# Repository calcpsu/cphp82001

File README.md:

# CalcPack HP 82001

A Li-Po battery replacement design for HP35/HP45/HP55/HP65/HP67 calculators. The original batteries had ~ 500mAh capacity, while modern Ni-MH replacements are typically ~1500mAh.

Li-Po has the advantage of far reduced self-discharge in comparison to Ni-MH, which is an advantage for an intermittently-used device. Even with similar mAh capacity, we can expect longer battery life.

Ni-MH / Ni-CD batteries are notorious for leaking. While Lithium Ion batteries are notorious for self-immolation, a well protected Li-Po battery (particularly in a low current application like this) should be able to be made very safe.

## Features / design goals:
- Fit into existing compartment with no modifications
- Similar or ideally exceed capacity of standard Ni-Cd or Ni-MH 3xAA types (1200~2200mAh)
- Dual charge - USB (externally) or in-place using original HP charger
- Battery charge control and protection
- Maximise battery life:
    - Minimise Iq to maximise time between charges (shelf time)
    - Minimise voltage drop / series resistance of circuits to maximise run time
    - Optimise Vout to minimise calculator power consumption

## References 
This has been inspired by the below reference projects:
 - https://www.edn.com/classic-hp-35-calculator-comes-back-to-life/
   - GOOD: Regulated (see reasoning in the article, and discussion below)
   - BAD: Has no charging circuit / must remove to charge
   - BAD: Cannot connect HP charger (would cause dangerous overcharge condition; best case trip battery OC protection)
 - https://hackaday.io/project/175815-classic-hp-calculator-lipo-battery-pack
   - GOOD: Has on-board charge controller
   - BAD: Has no regulation
   - GOOD: Can connect HP charger, but
   - BAD: Unable to charge from HP charger / must remove to charge

## Key Components
If you're looking for a full BOM, please check the main files.
A digikey list is provided here for convenience (no guarantees!): [calcpsu cphp82001](https://www.digikey.com.au/en/mylists/list/Z6K09H5IB0)
 - Battery:
     - 10x34x50mm lipo pouch cell. These also include a DW01A/FS8205 protection circuit.
 - Charge controller: [BQ21040](https://www.ti.com/lit/ds/symlink/bq21040.pdf)
     - Wide voltage input range (over voltage protected)
     - Clever voltage foldback mode (which will help with constant current supply charging)
     - Variable current setting
     - Safety timer (10h) and 10% termination current
 - OPTION 1: Regulator: [TLV75801](https://www.ti.com/lit/ds/symlink/tlv758p.pdf)
     - Ultra low dropout (~30mV)
     - 500mA current limited (enough for HP67 card read/write at ~400mA for a few seconds)
     - Very low Iq for a regulator (25uA at idle, assuming Vb > Vo; only 400uA or so at full current)
     - Note: option eliminated as of REV5; if you're really keen for a regulated version please to check out rev4.
 - OPTION 2: Current Limiter: [MCP380SNT](https://www.onsemi.com/pdf/datasheet/ncp380-d.pdf)
     - Designed as a USB input current limiter, also works for LiPo cell voltage range
     - 800mA limiting, short circuit protection
     - Provides the similar current limiting capability as the TLV75801 with minimal additional quiescent current; allows retaining this function/protection in case of an unregulated option.
 - Output protection diode: [MAX40203](https://www.analog.com/media/en/technical-documentation/data-sheets/MAX40203.pdf)
     - Low voltage drop (~40mV) ideal diode
     - Low leakage and low Iq (<0.5uA)
 - Undervoltage protection: [APX809S-31SA](https://www.diodes.com/assets/Datasheets/APX809S-810S.pdf)
     - Pre-set with 3.1V threshold
     - Output used to shutdown regulator, shutting off load and vastly reducing Iq
     - Actual protective disconnection of battery done at ~2.5V by battery pack protection circuit (typically DW01A/FS8205)
 - Input overvoltage protection: [NCP360SNT](https://www.onsemi.com/pdf/datasheet/ncp360-d.pdf)
     - Cuts off USB input for overvoltage condition (note that 2x rated voltage is required by compliance test standard EN38.3 T.7, required for transport of lipo batteries in USA/EU).
     - Input via pads does not require OVP - it can tolerate the required 22v/100mA required condition.

## Function Description

### Discharging, calculator on:
 - B+ supplies cell voltage via current limiting IC
 - Output delivered to calculator via ideal diode U3
 - Vout at 3.8V is below threshold for U4 (4.4V), Q2 is off and VCC is 0V (charging IC shutdown completely)
### Charging, USB:
 - VBUS supplies VCC via U6 and D1
 - Presence of VBUS pulls prog down via Q1, charge controller now charges battery at higher current (0.2C target)
 - Physically not possible to do inside the calculator, can assume calculator is not connected during charging.
   - Although, body diode of Q2 and U3 would enable effective load sharing in this case, with output at about 4V (still well within acceptable limits for the calculator). This could be used for a future alternative in-system charging connection (e.g. a modified charging circuit, wireless charging, etc.)
### Charging, HP charger:
 - HP charger supplies 50mA constant current, up to 16V (!!). With the original NiCads, these acted as a voltage clamp (float charge about 1.43V/cell = 4.3V) - we need to replace this function.
    - With no charging current, voltage Vout rises until U3 switches off.
    - Will continue to rise until clamped by D2 (this should be low enough to protect HP65/67 sense chip from harm with extended application, but too low will result in excessive Iq as the voltage nears the zener's knee). Reviewing available documents, 4.3V is definitely OK, 6.25V might be survivable (as this is Vss normally). I have tested with 5.6V zener, and this has shown no negative impact to any calculators (particualrly the HP-67, where the sense chip sees this voltage, albeit when off).
    - Exceeding 4.4V for 240ms, U4 activates and connects Vout to Vcc via Q2 and D4.
    - D4 ensures that U1 throttles current (Vcc below 4.3V) before U4 cuts off supply (VOUTF 4.4V), maximising utilisation of limited constant current supply. See further explanation in [issue #5](https://github.com/calcpsu/cphp82001/issues/5).
    - U1 begins charge cycle, delivering up to 50mA to battery.
    - On charge termination, VCC current is minimal (10's of uA), all 50mA will be running through D2 (~0.25W power; using biggest one I can fit to keep temperature down). Voltage will be at the zener voltage (5.6V).
 - HP35/45/55 calculators do not draw current when on - supplied separately by HP AC adapter, the calculator supply is physically disconnected from the charging circuit.
 - HP65/67 with card reader: card reader may draw from battery supply. The sense chip is connected to the battery continuously, and will see up to the 5.6V float voltage. In case the calculator is operated and this draws current, the CC supply voltage will drop until U4 shuts off current to the charge circuit, resetting the charge cycle. When VOUT drops below B+, U3 activates, and card reader is powered from the current limiter (B+). As the AC adapter is not sufficient to run the card reader, this is the least worst outcome available.
### Battery Exhausted:
 - HP35 shows low battery (decimal points) indication at V+ of 3.50V.
   - This represents about 6-7% charge state of LiPo
   - User may switch off and recharge now...
 - HP67 will show indicator at about 3.60V; similar to above but a little more margin.
 - HP35 will cease to function at ~3.25V, still draws ~75mA
   - User probably should switch off and recharge now...
 - U4 protects battery at VB+ = 3.1V, by disabling the regulator or current limiting IC. Iq should be ~10uA.
 - If left for a _really_ long time, VB+ may reduce to 2.5V, which should trigger battery pack protection circuit and fully disconnect the battery. Plugging in (turning on charge controller, which will do a battery detection routine and reset the protection circuit) will reset.

## Assembly Notes ##

Refer to the schematic for details. The following notes are worth considering if building your own:
* The design up to v4 allows either regulated or unregulated option. From v5, only unregulated is supported (and recommended, see below).
  - For regulated (best for HP35), U2 regulator provides regulation and current limiting - U7 is not required and can be omitted and bypassed.
  - For unregulated (best for all later types), U2 is omitted and bypassed, and U7 is added to provide current limiting
* Digikey list is [here](https://www.digikey.com.au/en/mylists/list/Z6K09H5IB0)
* A 3-pin JST-SH (1.0mm pitch) connector is used for the battery. 1=pos, 2=temp, 3=neg
  - R13 is in parallel with TS pin NTC thermistor. If the battery does not a provide NTC thermistor (white wire, 3 pin connector), leave pin2 open and install R13=10k.
  - Note datasheet indicates 237k resistor prevents timer disable mode, but this also prevents charging without thermistor
    
| R13 | Battery With Temperature Sensor | Battery Without Temperature Sensor |
| --- | --- | --- |
| Omit | 🟢 10% Current Charge Termination <br> 🟢 10h Charge Timeout | 🔴 10% Current Charge Termination <br> 🔴 10h Charge Timeout |
| 10k  | ⚠️ Will not charge T>25C <br> ⚠️ Will charge T<0C  | 🟢 10% Current Charge Termination <br> 🟢  charge timeout |

* Two case sizes are provided:
    * 8mm suits 8mm thick batteries (1500mAh)
    * 10mm suits 10mm thick batteries (2000mAh), but it has been noted this can be a tight fit in some calculators
* Variants of each case, with and without an LED hole, are provided. If you 3D print with a transluscent material, the hole is not needed!

## Notes on optimisation:

Addition of a series regulator is not an immediately obvious means to maximise efficiency. I've measured the HP-35 increases current consumption as voltage rises (this is most likely a result of the way the LEDs are driven with fixed-duty inductive energy, this appears as brighter leds). Even accounting for the linear loss and Iq of the regulator circuit, total power consumption decreases as the regulator voltage decreases (down to about 3.6V, the minimum to operate the calculator reliably). The newer models (HP-45, HP-67) do the opposite - the current drops as the voltage increases, which indicates a more typical profile for a switchmode converter. The HP-67 has a card reader with a motor; this draws around 400mA when reading/writing a card, direct from battery. To allow for a little drop in the system, the regulator voltage needs to be a touch higher (looks like about 3.8V works consistently).

### Why not a switching regulator?

In theory, replacing the series linear regulator with a switching regulator may allow use of the battery capacity right down to 3.1V, and more efficiently use the currently wasted energy of the full battery (VB+ > 3.78V) currently being dissipated by the linear reg.

I've investigated using a MIC2250 step-up regulator, which has a surprisingly low Iq (55uA, not switching), and could provide a consistent output voltage right down to the end of the battery capacity (Vb=3.0V). At the currents needed, this can be around 87% efficient. This would provide a consistent voltage right up until shutdown. While this might be good particularly for the HP-67 card reader, it has the disadvantage of skipping the calculator's built-in low battery indication - the power supply unit would completely shutdown without any warning with a low battery.

### Model of 3 options

I've done a simulation of the 3 options:

  1. No regulator (default - calculator supplied with battery voltage via MAX40203 diode)
  2. Linear regulator (TLV75801, set to 3.80V)
  3. Switchmode step-up regulator (MIC2250, set to 3.80V also)

For each, the model calculates the change in output voltages given the battery state, calculator and power supply current draw, and iterates until the battery (2000mAh) is exhausted. The calculator load is measured from 3 sample calculators (HP-35, HP-45 and HP-67), reflecting the calculator being left on in the default display ("0." or "0.00" depending on the model), and accounts for the changing current with changing supply voltage. Results are shown below.

In summary, a regulated design gains a slight advantage in run time for the HP-35, while slightly reducing run time for HP-45 and HP-67. The switchmode design is actually best for the current-hungry HP-67, but not by a significant amount, and at the cost of higher quiescent current (shortening standby time significantly).

In conclusion, the regulated design provides a slight advantage for the HP-35 based on this model, however the unregulated design (with addition of necessary output short-circuit protection / current limiter) can be expected to be ideal for other models. Prototype testing with rev 3.5 showed the unregulated design works well in all the calculators, and the regulated design had noticeably faster self-discharge in practice, particularly as the quiescent current is larger than anticipated in dropout mode. As such, further designs have eliminated the regulator in favour of improved board layout and ease of use.

#### Results summary (t in hours)

#### HP-35

#### HP-45

#### HP-67

## Community Builds ##
Built one? Send me some pics and I'll share here!
### [Milo van der Zee](https://github.com/MilovdZee) ###

## License

This work is licensed under a
[Creative Commons Attribution-NonCommercial-ShareAlike 4.0 International License][cc-by-nc-sa].

[![CC BY-NC-SA 4.0][cc-by-nc-sa-image]][cc-by-nc-sa]

[cc-by-nc-sa]: http://creativecommons.org/licenses/by-nc-sa/4.0/
[cc-by-nc-sa-image]: https://licensebuttons.net/l/by-nc-sa/4.0/88x31.png
[cc-by-nc-sa-shield]: https://img.shields.io/badge/License-CC%20BY--NC--SA%204.0-lightgrey.svg

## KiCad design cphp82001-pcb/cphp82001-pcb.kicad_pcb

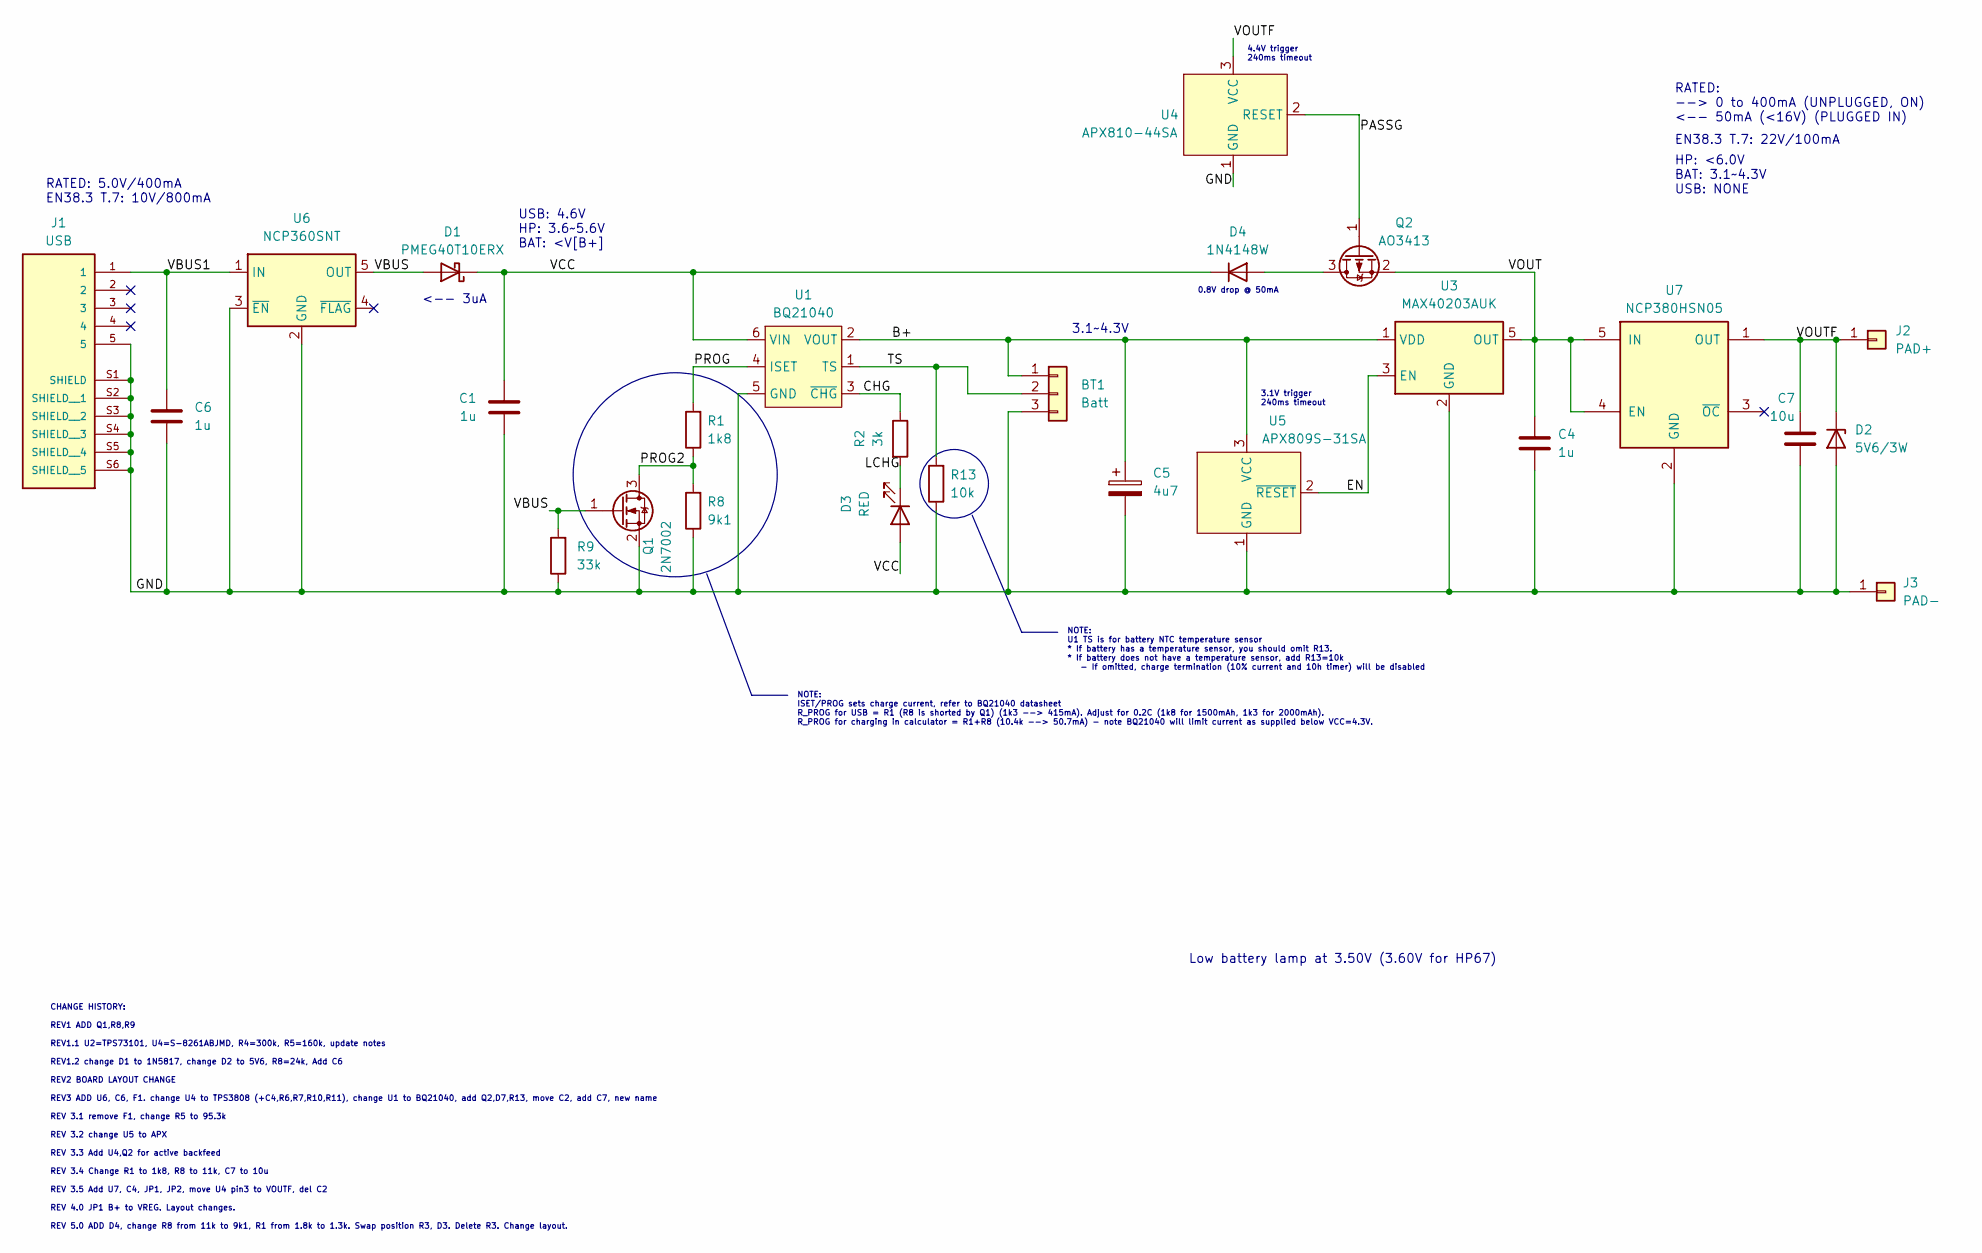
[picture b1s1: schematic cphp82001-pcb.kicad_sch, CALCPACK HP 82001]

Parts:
BT1: Batt; JST_SH_BM03B-SRSS-TB_1x03-1MP_P1.00mm_Vertical_13PADS
C1, C4, C6: 1u; C_0805_2012Metric
C5: 4u7; C_0805_2012Metric
C7: 10u; C_0805_2012Metric
D1: PMEG40T10ERX; D_SOD-123
D2: 5V6/3W; D_SMA
D3: RED; LED_0805_2012Metric
D4: 1N4148W; D_SOD-123
J1: USB; AMPHENOL_10118194-0001LF; PARTREV D
J2: PAD+; PAD_8x15
J3: PAD-; PAD_8x15
Q1: 2N7002; SOT-23
Q2: AO3413; SOT-23
R1: 1k8; R_0805_2012Metric
R2: 3k; R_0805_2012Metric
R8: 9k1; R_0805_2012Metric
R9: 33k; R_0805_2012Metric
R13: 10k; R_0805_2012Metric
U1: BQ21040; SOT-23-6_TI_DBV6
U3: MAX40203AUK; SOT-23-5_TI_DBV5
U4: APX810-44SA; SOT-23-3
U5: APX809S-31SA; SOT-23-3
U6: NCP360SNT; SOT-23-5_TI_DBV5
U7: NCP380HSN05; SOT-23-5_TI_DBV5

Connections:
/B+: BT1.1, C5.1, U1.2 (VOUT), U3.1 (VDD), U5.3 (VCC)
/CHG: R2.1, U1.3 (~CHG)
/EN: U3.3 (EN), U5.2 (~RESET)
/GND: BT1.3, C1.2, C4.2, C5.2, C6.2, C7.2, D2.2 (A), J1.5, J1.S1 (SHIELD), J1.S2 (SHIELD__1), J1.S3 (SHIELD__2), J1.S4 (SHIELD__3), J1.S5 (SHIELD__4), J1.S6 (SHIELD__5), J3.1, Q1.2 (S), R8.1, R9.1, R13.1, U1.5 (GND), U3.2 (GND), U4.1 (GND), U5.1 (GND), U6.2 (GND), U6.3 (~EN), U7.2 (GND)
/LCHG: D3.1 (K), R2.2
/PASSG: Q2.1 (G), U4.2 (RESET)
/PROG: R1.2, U1.4 (ISET)
/PROG2: Q1.3 (D), R1.1, R8.2
/TS: BT1.2, R13.2, U1.1 (TS)
/VBUS: D1.2 (A), Q1.1 (G), R9.2, U6.5 (OUT)
/VBUS1: C6.1, J1.1, U6.1 (IN)
/VCC: C1.1, D1.1 (K), D3.2 (A), D4.1 (K), U1.6 (VIN)
/VOUT: C4.1, Q2.2 (S), U3.5 (OUT), U7.4 (EN), U7.5 (IN)
/VOUTF: C7.1, D2.1 (K), J2.1, U4.3 (VCC), U7.1 (OUT)
unnamed: D4.2 (A), Q2.3 (D)

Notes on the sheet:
<-- 3uA
NOTE: ISET/PROG sets charge current, refer to BQ21040 datasheet R_PROG for USB = R1 (R8 is shorted by Q1) (1k3 --> 415mA). Adjust for 0.2C (1k8 for 1500mAh, 1k3 for 2000mAh). R_PROG for charging in calculator = R1+R8 (10.4k --> 50.7mA) - note BQ21040 will limit current as supplied below VCC=4.3V.
HP: <6.0V BAT: 3.1~4.3V USB: NONE
EN38.3 T.7: 22V/100mA
3.1V trigger 240ms timeout
RATED: --> 0 to 400mA (UNPLUGGED, ON) <-- 50mA (<16V) (PLUGGED IN)
USB: 4.6V HP: 3.6~5.6V BAT: <V[B+]
3.1~4.3V
NOTE: U1 TS is for battery NTC temperature sensor * If battery has a temperature sensor, you should omit R13. * If battery does not have a temperature sensor, add R13=10k - If omitted, charge termination (10% current and 10h timer) will be disabled
4.4V trigger 240ms timeout
RATED: 5.0V/400mA EN38.3 T.7: 10V/800mA
0.8V drop @ 50mA
CHANGE HISTORY: REV1 ADD Q1,R8,R9 REV1.1 U2=TPS73101, U4=S-8261ABJMD, R4=300k, R5=160k, update notes REV1.2 change D1 to 1N5817, change D2 to 5V6, R8=24k, Add C6 REV2 BOARD LAYOUT CHANGE REV3 ADD U6, C6, F1. change U4 to TPS3808 (+C4,R6,R7,R10,R11), change U1 to BQ21040, add Q2,D7,R13, move C2, add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
Low battery lamp at 3.50V (3.60V for HP67)

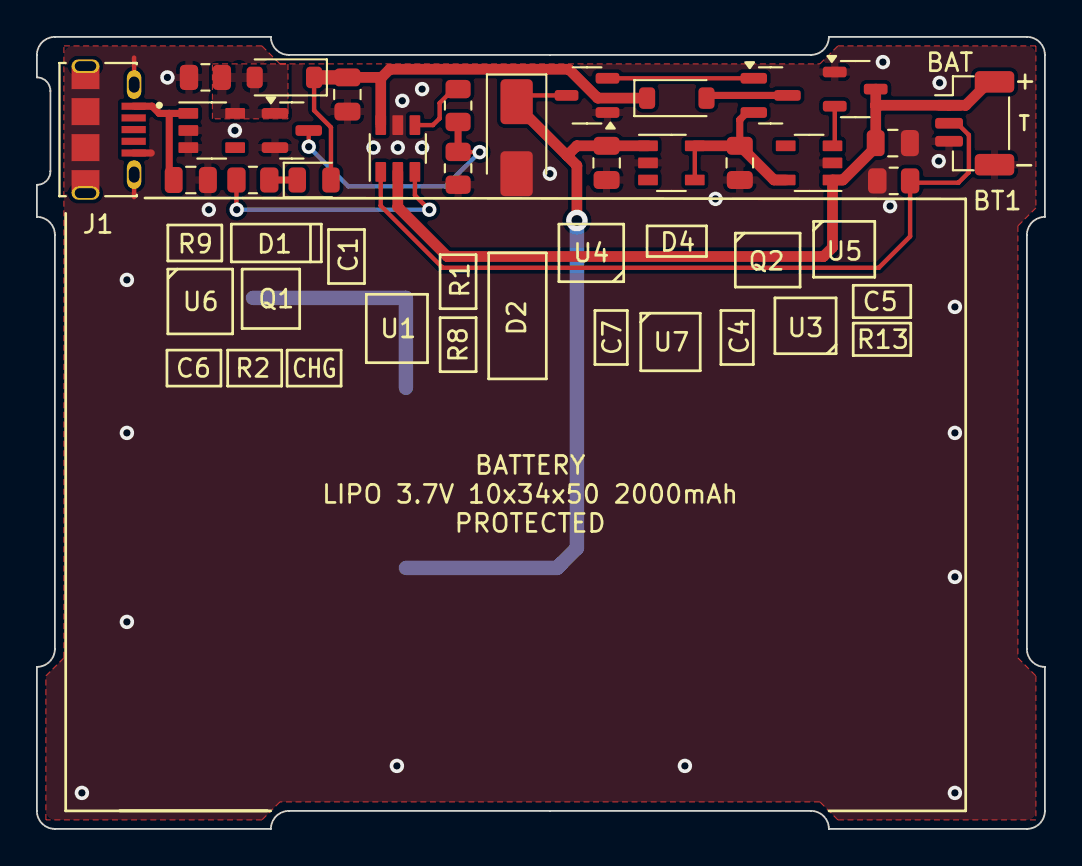
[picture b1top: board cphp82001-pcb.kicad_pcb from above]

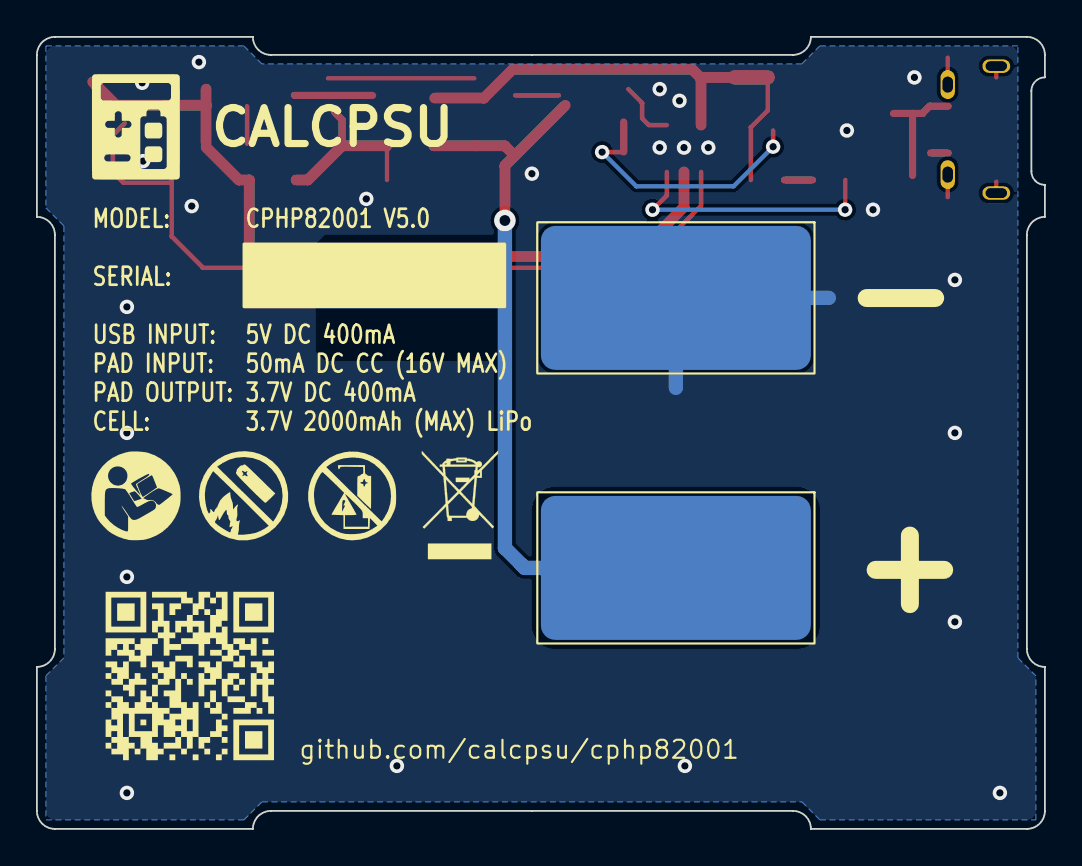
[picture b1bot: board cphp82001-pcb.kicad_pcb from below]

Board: 2 copper layers, 56.0 x 44.0 mm, 26 parts (2 on the bottom side), 15 nets.

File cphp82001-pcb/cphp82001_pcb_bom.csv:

Reference,Value,Datasheet,Footprint,Qty,DNP
BT1,Batt,~,george:JST_SH_BM03B-SRSS-TB_1x03-1MP_P1.00mm_Vertical_13PADS,1,
"C1,C4,C6",1u,~,Capacitor_SMD:C_0805_2012Metric,3,
C5,4u7,~,Capacitor_SMD:C_0805_2012Metric,1,
C7,10u,~,Capacitor_SMD:C_0805_2012Metric,1,
D1,PMEG40T10ERX,http://www.vishay.com/docs/88525/1n5817.pdf,Diode_SMD:D_SOD-123,1,
D2,5V6/3W,~,Diode_SMD:D_SMA,1,
D3,RED,~,LED_SMD:LED_0805_2012Metric,1,
D4,1N4148W,https://www.vishay.com/docs/85748/1n4148w.pdf,Diode_SMD:D_SOD-123,1,
J1,USB,,mod_local:AMPHENOL_10118194-0001LF,1,
J2,PAD+,~,george:PAD_8x15,1,
J3,PAD-,~,george:PAD_8x15,1,
Q1,2N7002,https://www.onsemi.com/pub/Collateral/NDS7002A-D.PDF,Package_TO_SOT_SMD:SOT-23,1,
Q2,AO3413,http://www.aosmd.com/pdfs/datasheet/AO3401A.pdf,Package_TO_SOT_SMD:SOT-23,1,
R1,1k8,~,Resistor_SMD:R_0805_2012Metric,1,
R2,3k,~,Resistor_SMD:R_0805_2012Metric,1,
R8,9k1,~,Resistor_SMD:R_0805_2012Metric,1,
R9,33k,~,Resistor_SMD:R_0805_2012Metric,1,
R13,10k,~,Resistor_SMD:R_0805_2012Metric,1,
U1,BQ21040,https://www.ti.com/lit/ds/symlink/bq21040.pdf,george:SOT-23-6_TI_DBV6,1,
U3,MAX40203AUK,https://datasheets.maximintegrated.com/en/ds/MAX40200.pdf,george:SOT-23-5_TI_DBV5,1,
U4,APX810-44SA,https://www.diodes.com/assets/Datasheets/APX803S.pdf,Package_TO_SOT_SMD:SOT-23-3,1,
U5,APX809S-31SA,https://www.diodes.com/assets/Datasheets/APX803S.pdf,Package_TO_SOT_SMD:SOT-23-3,1,
U6,NCP360SNT,https://www.onsemi.com/pdf/datasheet/ncp349-d.pdf,george:SOT-23-5_TI_DBV5,1,
U7,NCP380HSN05,http://www.ti.com/lit/ds/symlink/tps2041.pdf,george:SOT-23-5_TI_DBV5,1,

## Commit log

2024-01-09 rev3 pcb
2024-01-09 add docs
2024-01-09 old board revisions - plots and schematics
2024-01-09 move schematic to plot (rev2)
2024-01-09 move old plots to pcb folder
2024-01-09 plot rev3
2024-01-10 Create LICENSE
2024-01-10 move component 3d models to pcb folder
2024-01-10 Update rev3
2024-01-10 Export 3d step file pcb
2024-01-10 Plot rev3.1
2024-01-12 board layout update
2024-01-12 images
2024-01-12 rename
2024-01-12 Updates to model
2024-01-14 Update power model
2024-01-14 update figures
2024-01-15 Update board and render (v3.1)
2024-01-15 A few more updates (v3.1)
2024-01-22 Rev3.2
2024-01-23 rev3.3
2024-01-23 rev3.3a
2024-01-29 rev3.3 final
2024-01-29 Update model for Iq
2024-04-16 Minor update
2024-04-17 rev3.5
2024-09-09 Update case 3d files
2024-09-16 Add Milo's build images
    Thank you!
2024-09-24 Rev 4.0
2024-09-24 Update schematic notes
2024-09-25 Update to charge termination R13 instructions
2024-09-25 Amend instructions after testing
2024-09-26 Amend BOM
    Misaligned with
2024-09-26 Missing files from power model
2024-10-15 rev5
2024-11-07 add 8mm case option
2024-11-26 Updated BOM
2025-02-19 Minor update to BOM
2025-02-19 Refresh 3D file
2025-02-19 Minor change to case
    Add cutout to enable v3.5 diode modification (v3.5A).
